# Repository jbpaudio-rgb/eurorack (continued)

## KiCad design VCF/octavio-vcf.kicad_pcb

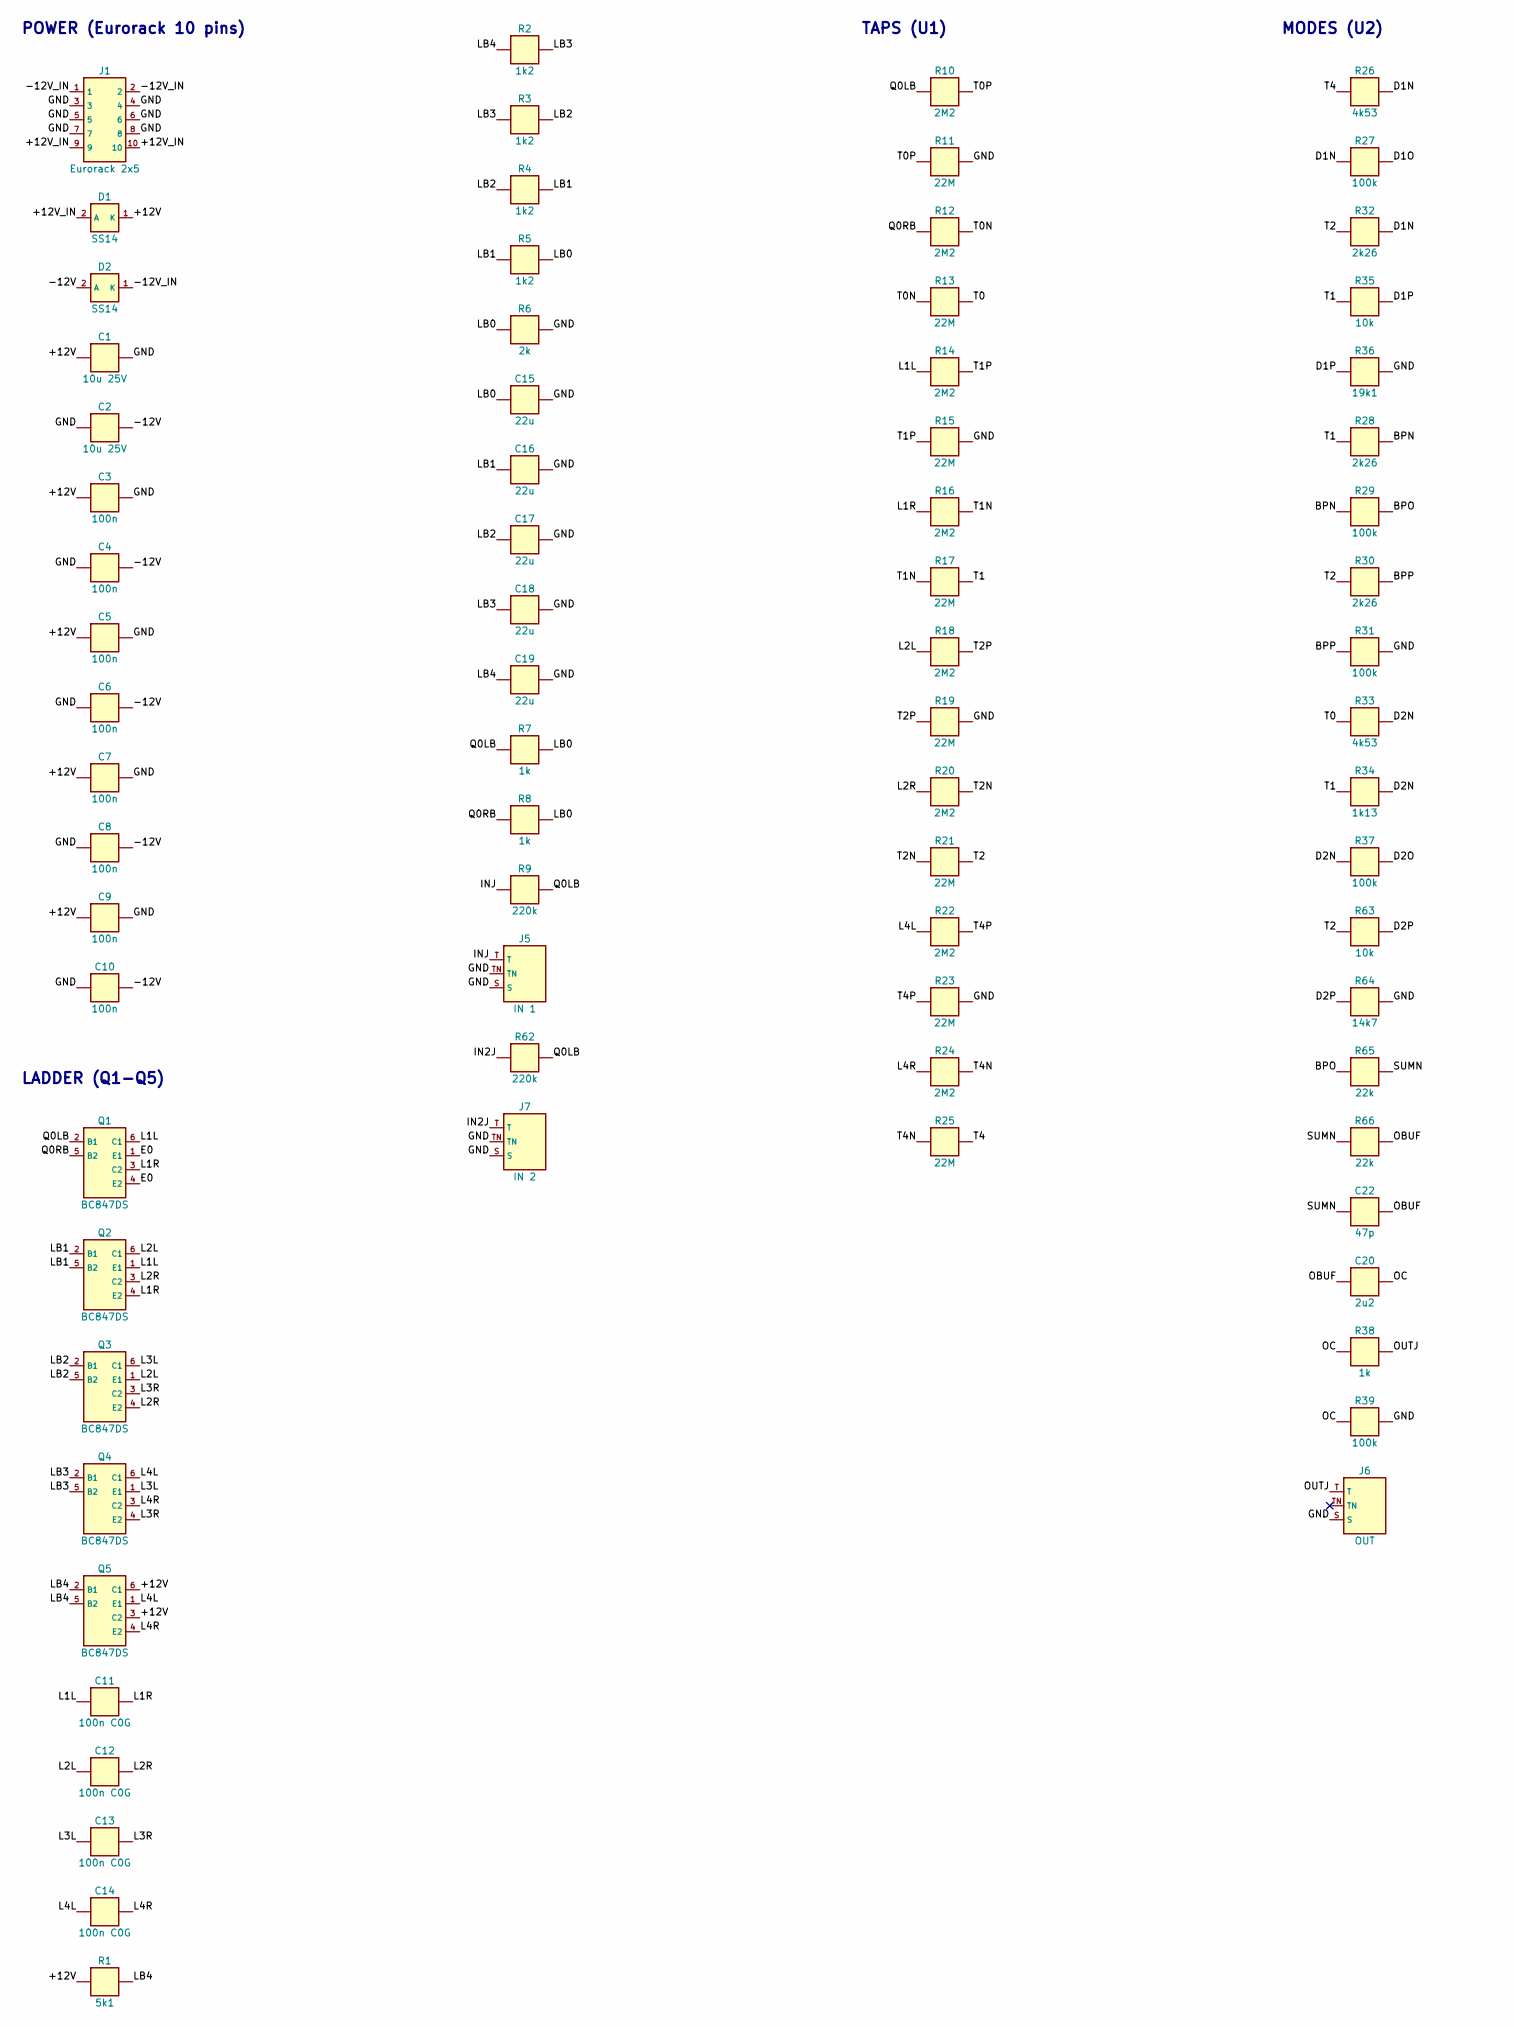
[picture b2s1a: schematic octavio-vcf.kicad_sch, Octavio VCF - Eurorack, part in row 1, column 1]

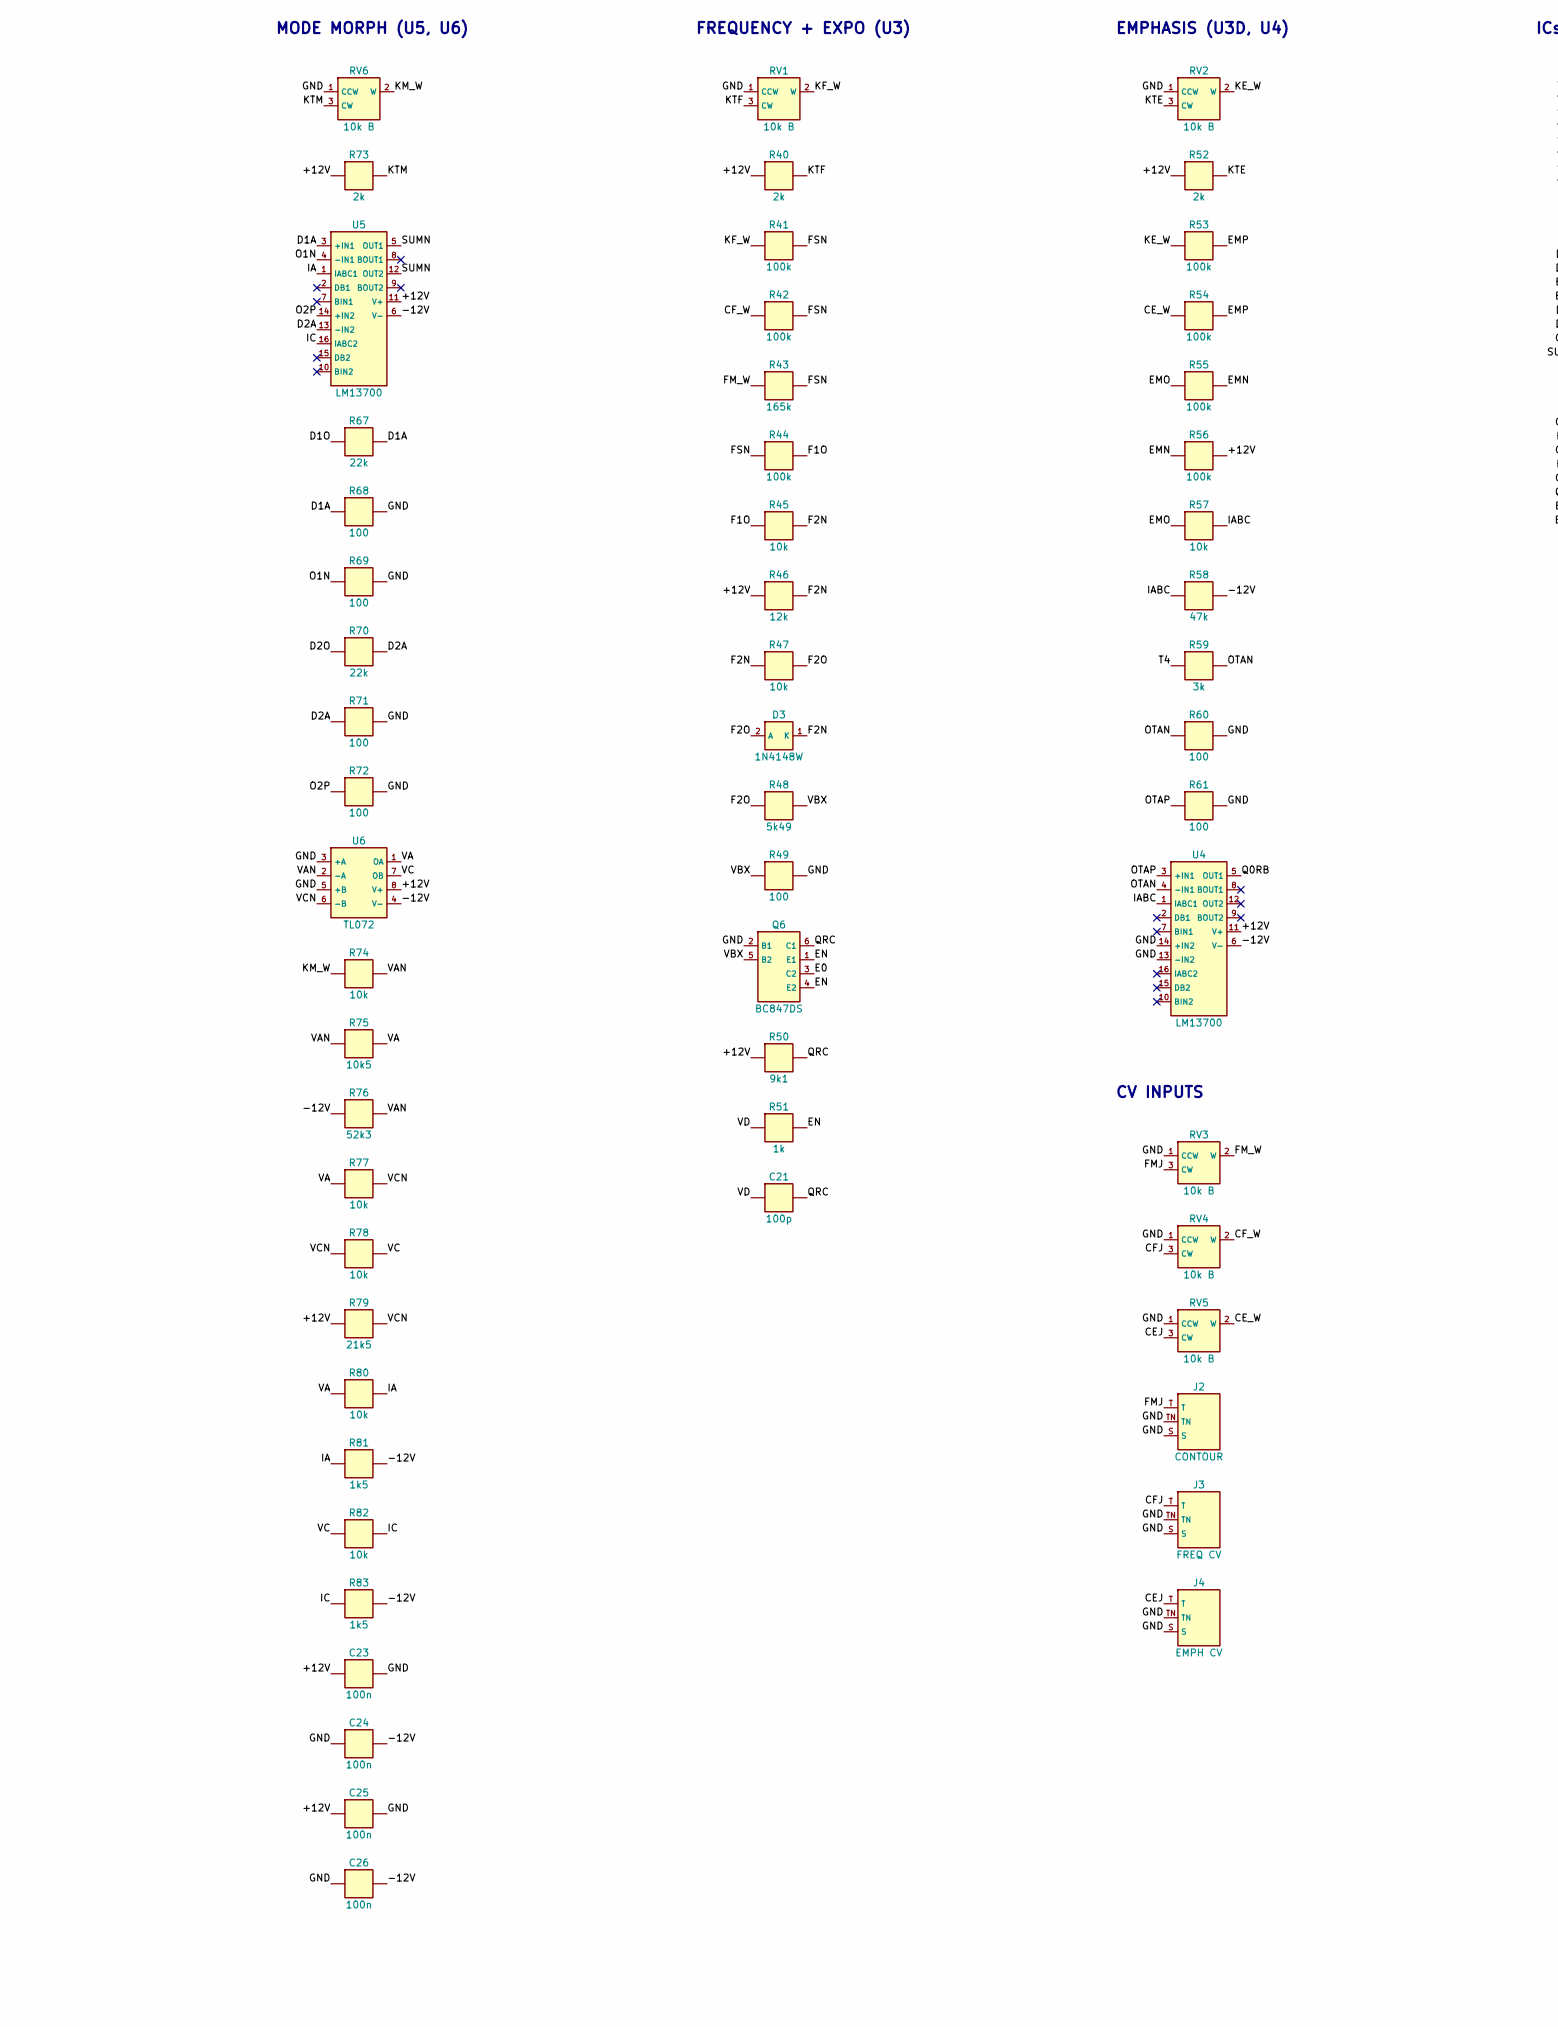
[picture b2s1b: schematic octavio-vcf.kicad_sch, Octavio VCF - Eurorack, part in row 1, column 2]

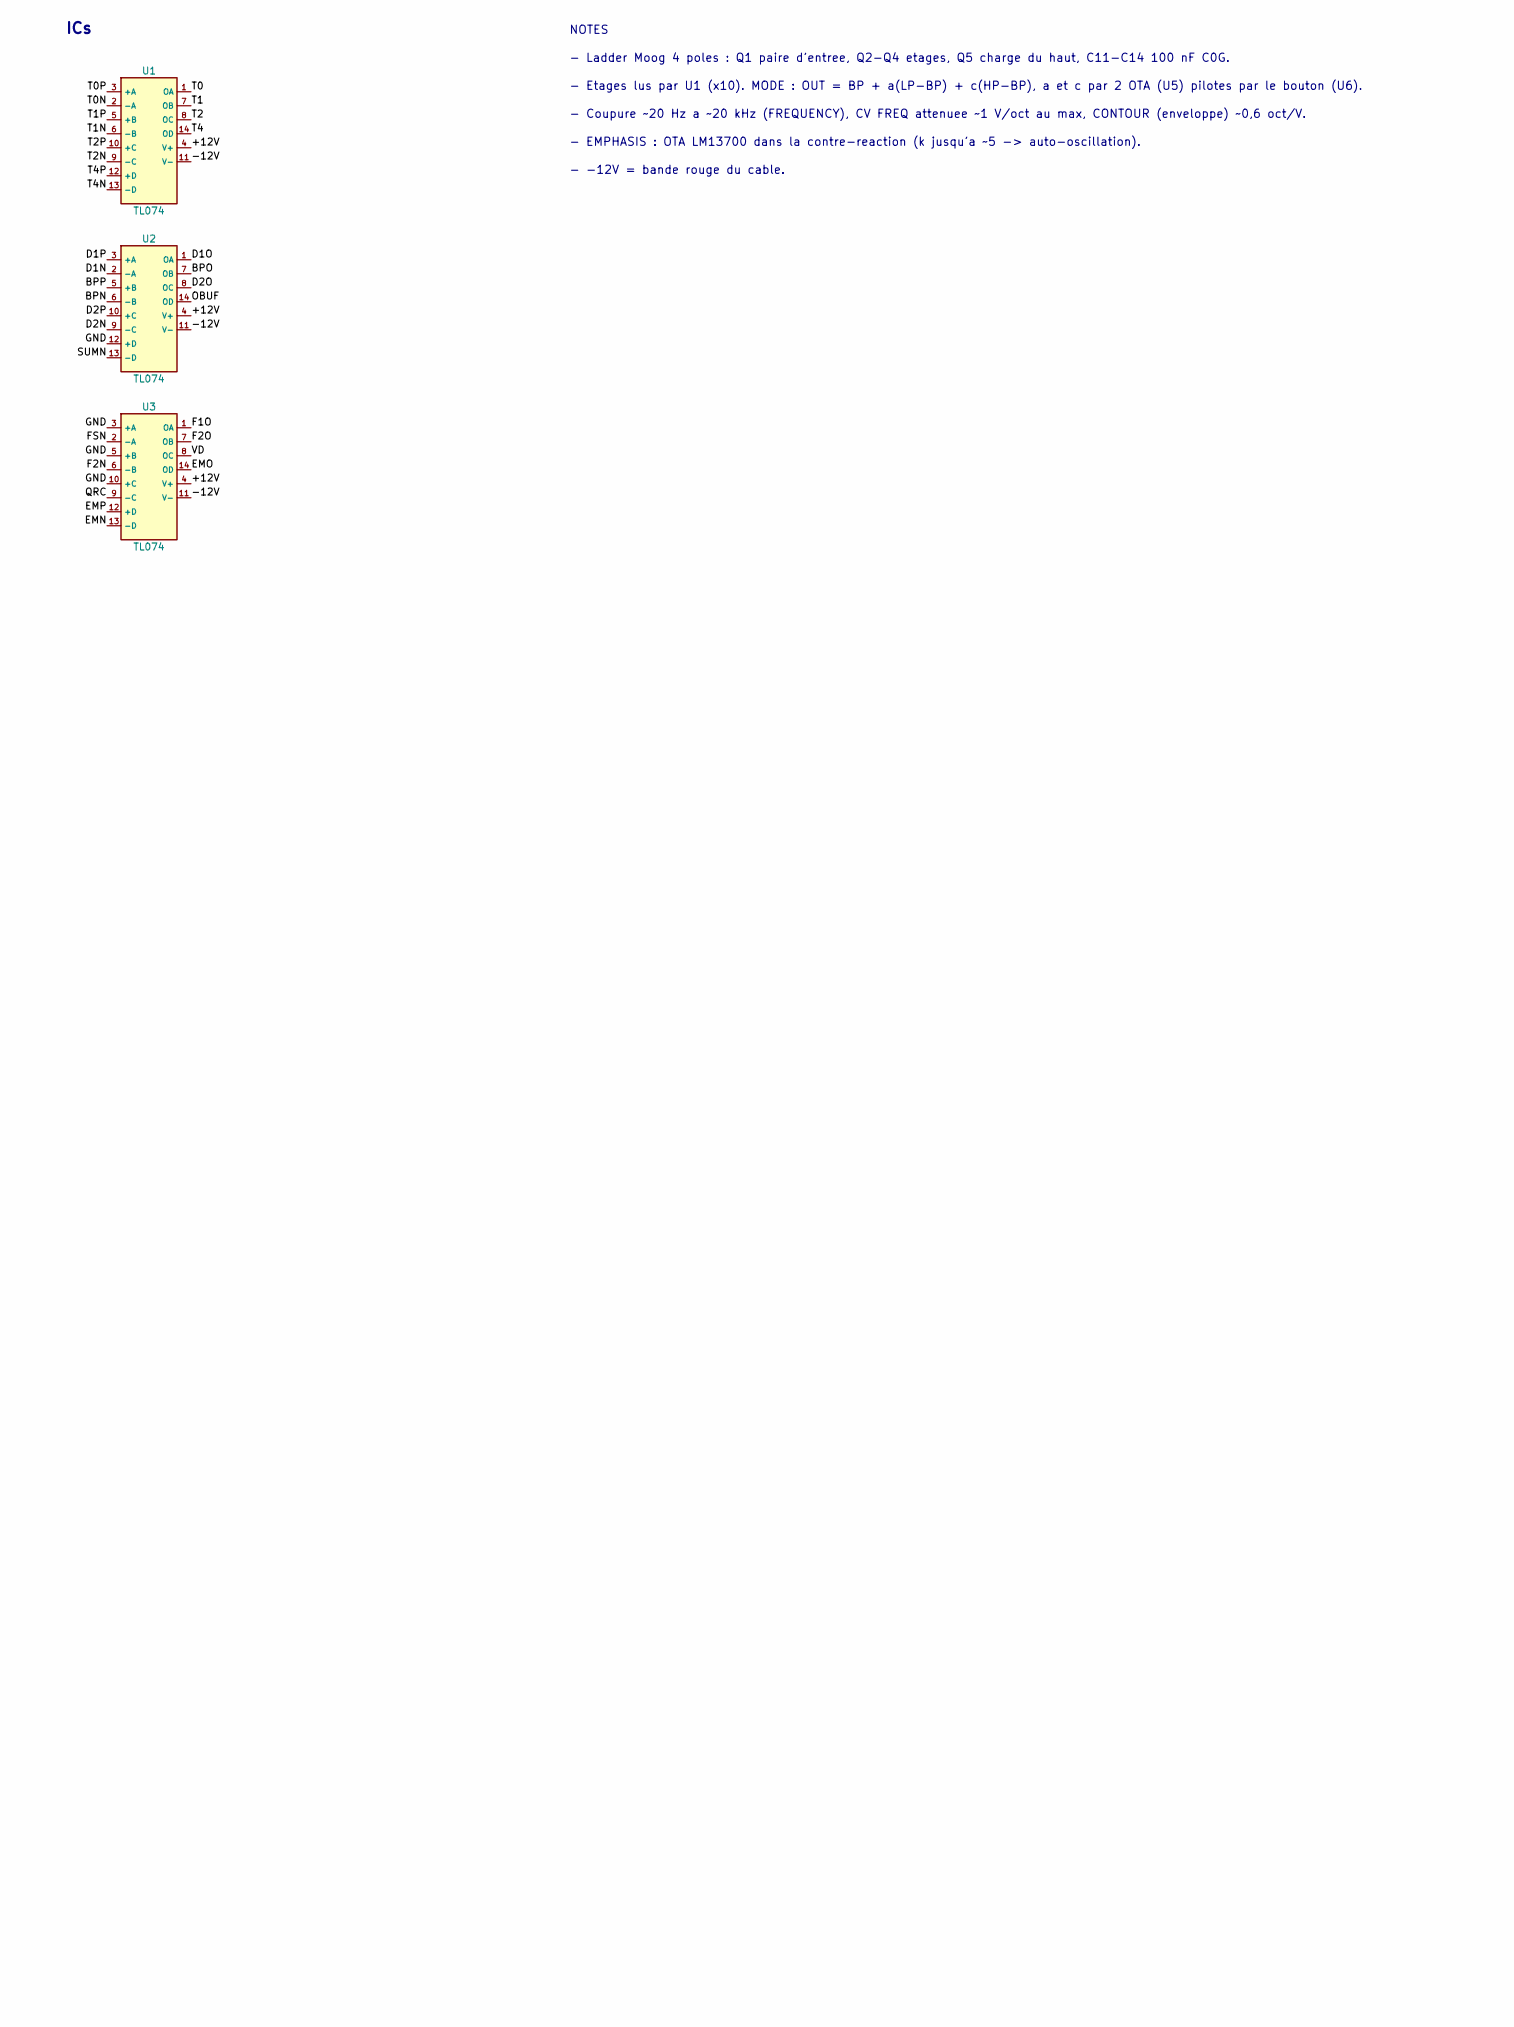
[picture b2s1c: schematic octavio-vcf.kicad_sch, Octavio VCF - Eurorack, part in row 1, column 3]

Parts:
C1, C2: 10u 25V; C_1206_3216Metric; MPN X5R/X7R 1206
C3, C4, C5, C6, C7, C8, C9, C10, C23, C24, C25, C26: 100n; C_0805_2012Metric
C11, C12, C13, C14: 100n C0G; C_1206_3216Metric; MPN 100 nF C0G/NP0 1206 2 % (condensateur d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
C15, C16, C17, C18, C19: 22u; C_1206_3216Metric; MPN X5R 1206 16 V
C20: 2u2; C_1206_3216Metric; MPN X7R 1206 25 V
C21: 100p; C_0805_2012Metric
C22: 47p; C_0805_2012Metric
D1, D2: SS14; D_SMA; MPN SS14 (40 V 1 A Schottky)
D3: 1N4148W; D_SOD-123; MPN 1N4148W
J1: Eurorack 2x5; IDC-Header_2x05_P2.54mm_Vertical; MPN Shrouded header 2x5 2.54 mm
J2: CONTOUR; Jack_3.5mm_Thonkiconn_PJ398SM; MPN QingPu WQP-PJ301M-12 (Thonkiconn)
J3: FREQ CV; Jack_3.5mm_Thonkiconn_PJ398SM; MPN QingPu WQP-PJ301M-12 (Thonkiconn)
J4: EMPH CV; Jack_3.5mm_Thonkiconn_PJ398SM; MPN QingPu WQP-PJ301M-12 (Thonkiconn)
J5: IN 1; Jack_3.5mm_Thonkiconn_PJ398SM; MPN QingPu WQP-PJ301M-12 (Thonkiconn)
J6: OUT; Jack_3.5mm_Thonkiconn_PJ398SM; MPN QingPu WQP-PJ301M-12 (Thonkiconn)
J7: IN 2; Jack_3.5mm_Thonkiconn_PJ398SM; MPN QingPu WQP-PJ301M-12 (Thonkiconn)
Q1, Q2, Q3, Q4, Q5, Q6: BC847DS; SOT-457; MPN BC847DS,115 (Nexperia, paire double)
R1: 5k1; R_0805_2012Metric
R2, R3, R4, R5: 1k2; R_0805_2012Metric
R6, R40, R52, R73: 2k; R_0805_2012Metric
R7, R8, R38, R51: 1k; R_0805_2012Metric
R9, R62: 220k; R_0805_2012Metric
R10, R12, R14, R16, R18, R20, R22, R24: 2M2; R_0805_2012Metric
R11, R13, R15, R17, R19, R21, R23, R25: 22M; R_0805_2012Metric
R26, R33: 4k53; R_0805_2012Metric
R27, R29, R31, R37, R39, R41, R42, R44, R53, R54, R55, R56: 100k; R_0805_2012Metric
R28, R30, R32: 2k26; R_0805_2012Metric
R34: 1k13; R_0805_2012Metric
R35, R45, R47, R57, R63, R74, R77, R78, R80, R82: 10k; R_0805_2012Metric
R36: 19k1; R_0805_2012Metric
R43: 165k; R_0805_2012Metric
R46: 12k; R_0805_2012Metric
R48: 5k49; R_0805_2012Metric
R49, R60, R61, R68, R69, R71, R72: 100; R_0805_2012Metric
R50: 9k1; R_0805_2012Metric
R58: 47k; R_0805_2012Metric
R59: 3k; R_0805_2012Metric
R64: 14k7; R_0805_2012Metric
R65, R66, R67, R70: 22k; R_0805_2012Metric
R75: 10k5; R_0805_2012Metric
R76: 52k3; R_0805_2012Metric
R79: 21k5; R_0805_2012Metric
R81, R83: 1k5; R_0805_2012Metric
RV1, RV2, RV3, RV4, RV5, RV6: 10k B; Pot_Alpha_9mm_Vertical; MPN POT-R09V-10K (9 mm vertical, B10k)
U1, U2, U3: TL074; SOIC-14_3.9x8.7mm_P1.27mm; MPN TL074CDR
U4, U5: LM13700; SOIC-16_3.9x9.9mm_P1.27mm; MPN LM13700MX/NOPB
U6: TL072; SOIC-8_3.9x4.9mm_P1.27mm; MPN TL072CDR

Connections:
+12V: C1.1, C3.1, C5.1, C7.1, C9.1, C23.1, C25.1, D1.1 (K), Q5.3 (C2), Q5.6 (C1), R1.1, R40.1, R46.1, R50.1, R52.1, R56.2, R73.1, R79.1, U1.4 (V+), U2.4 (V+), U3.4 (V+), U4.11 (V+), U5.11 (V+), U6.8 (V+)
+12V_IN: D1.2 (A), J1.9, J1.10
-12V: C2.2, C4.2, C6.2, C8.2, C10.2, C24.2, C26.2, D2.2 (A), R58.2, R76.1, R81.2, R83.2, U1.11 (V-), U2.11 (V-), U3.11 (V-), U4.6 (V-), U5.6 (V-), U6.4 (V-)
-12V_IN: D2.1 (K), J1.1, J1.2
BPN: R28.2, R29.1, U2.6 (-B)
BPO: R29.2, R65.1, U2.7 (OB)
BPP: R30.2, R31.1, U2.5 (+B)
CEJ: J4.T, RV5.3 (CW)
CE_W: R54.1, RV5.2 (W)
CFJ: J3.T, RV4.3 (CW)
CF_W: R42.1, RV4.2 (W)
D1A: R67.2, R68.1, U5.3 (+IN1)
D1N: R26.2, R27.1, R32.2, U2.2 (-A)
D1O: R27.2, R67.1, U2.1 (OA)
D1P: R35.2, R36.1, U2.3 (+A)
D2A: R70.2, R71.1, U5.13 (-IN2)
D2N: R33.2, R34.2, R37.1, U2.9 (-C)
D2O: R37.2, R70.1, U2.8 (OC)
D2P: R63.2, R64.1, U2.10 (+C)
E0: Q1.1 (E1), Q1.4 (E2), Q6.3 (C2)
EMN: R55.2, R56.1, U3.13 (-D)
EMO: R55.1, R57.1, U3.14 (OD)
EMP: R53.2, R54.2, U3.12 (+D)
EN: Q6.1 (E1), Q6.4 (E2), R51.2
F1O: R44.2, R45.1, U3.1 (OA)
F2N: D3.1 (K), R45.2, R46.2, R47.1, U3.6 (-B)
F2O: D3.2 (A), R47.2, R48.1, U3.7 (OB)
FMJ: J2.T, RV3.3 (CW)
FM_W: R43.1, RV3.2 (W)
FSN: R41.2, R42.2, R43.2, R44.1, U3.2 (-A)
GND: C1.2, C2.1, C3.2, C4.1, C5.2, C6.1, C7.2, C8.1, C9.2, C10.1, C15.2, C16.2, C17.2, C18.2, C19.2, C23.2, C24.1, C25.2, C26.1, J1.3, J1.4, J1.5, J1.6, J1.7, J1.8, J2.S, J2.TN, J3.S, J3.TN, J4.S, J4.TN, J5.S, J5.TN, J6.S, J7.S, J7.TN, Q6.2 (B1), R6.2, R11.2, R15.2, R19.2, R23.2, R31.2, R36.2, R39.2, R49.2, R60.2, R61.2, R64.2, R68.2, R69.2, R71.2, R72.2, RV1.1 (CCW), RV2.1 (CCW), RV3.1 (CCW), RV4.1 (CCW), RV5.1 (CCW), RV6.1 (CCW), U2.12 (+D), U3.3 (+A), U3.5 (+B), U3.10 (+C), U4.13 (-IN2), U4.14 (+IN2), U6.3 (+A), U6.5 (+B)
IABC: R57.2, R58.1, U4.1 (IABC1)
IN2J: J7.T, R62.1
INJ: J5.T, R9.1
KE_W: R53.1, RV2.2 (W)
KF_W: R41.1, RV1.2 (W)
KM_W: R74.1, RV6.2 (W)
KTE: R52.2, RV2.3 (CW)
KTF: R40.2, RV1.3 (CW)
KTM: R73.2, RV6.3 (CW)
L1L: C11.1, Q1.6 (C1), Q2.1 (E1), R14.1
L1R: C11.2, Q1.3 (C2), Q2.4 (E2), R16.1
L2L: C12.1, Q2.6 (C1), Q3.1 (E1), R18.1
L2R: C12.2, Q2.3 (C2), Q3.4 (E2), R20.1
L3L: C13.1, Q3.6 (C1), Q4.1 (E1)
L3R: C13.2, Q3.3 (C2), Q4.4 (E2)
L4L: C14.1, Q4.6 (C1), Q5.1 (E1), R22.1
L4R: C14.2, Q4.3 (C2), Q5.4 (E2), R24.1
LB0: C15.1, R5.2, R6.1, R7.2, R8.2
LB1: C16.1, Q2.2 (B1), Q2.5 (B2), R4.2, R5.1
LB2: C17.1, Q3.2 (B1), Q3.5 (B2), R3.2, R4.1
LB3: C18.1, Q4.2 (B1), Q4.5 (B2), R2.2, R3.1
LB4: C19.1, Q5.2 (B1), Q5.5 (B2), R1.2, R2.1
O1N: R69.1, U5.4 (-IN1)
O2P: R72.1, U5.14 (+IN2)
OBUF: C20.1, C22.2, R66.2, U2.14 (OD)
OC: C20.2, R38.1, R39.1
OTAN: R59.2, R60.1, U4.4 (-IN1)
OTAP: R61.1, U4.3 (+IN1)
OUTJ: J6.T, R38.2
Q0LB: Q1.2 (B1), R7.1, R9.2, R10.1, R62.2
Q0RB: Q1.5 (B2), R8.1, R12.1, U4.5 (OUT1)
QRC: C21.2, Q6.6 (C1), R50.2, U3.9 (-C)
SUMN: C22.1, R65.2, R66.1, U2.13 (-D), U5.5 (OUT1), U5.12 (OUT2)
T0: R13.2, R33.1, U1.1 (OA)
T0N: R12.2, R13.1, U1.2 (-A)
T0P: R10.2, R11.1, U1.3 (+A)
T1: R17.2, R28.1, R34.1, R35.1, U1.7 (OB)
T1N: R16.2, R17.1, U1.6 (-B)
T1P: R14.2, R15.1, U1.5 (+B)
T2: R21.2, R30.1, R32.1, R63.1, U1.8 (OC)
T2N: R20.2, R21.1, U1.9 (-C)
T2P: R18.2, R19.1, U1.10 (+C)
T4: R25.2, R26.1, R59.1, U1.14 (OD)
T4N: R24.2, R25.1, U1.13 (-D)
T4P: R22.2, R23.1, U1.12 (+D)
VA: R75.2, R77.1, R80.1, U6.1 (OA)
VAN: R74.2, R75.1, R76.2, U6.2 (-A)
VBX: Q6.5 (B2), R48.2, R49.1
VC: R78.2, R82.1, U6.7 (OB)
VCN: R77.2, R78.1, R79.2, U6.6 (-B)
VD: C21.1, R51.1, U3.8 (OC)

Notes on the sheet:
POWER (Eurorack 10 pins)
LADDER (Q1-Q5)
TAPS (U1)
MODES (U2)
MODE MORPH (U5, U6)
FREQUENCY + EXPO (U3)
EMPHASIS (U3D, U4)
CV INPUTS
ICs
NOTES
- Ladder Moog 4 poles : Q1 paire d'entree, Q2-Q4 etages, Q5 charge du haut, C11-C14 100 nF C0G.
- Etages lus par U1 (x10). MODE : OUT = BP + a(LP-BP) + c(HP-BP), a et c par 2 OTA (U5) pilotes par le bouton (U6).
- Coupure ~20 Hz a ~20 kHz (FREQUENCY), CV FREQ attenuee ~1 V/oct au max, CONTOUR (enveloppe) ~0,6 oct/V.
- EMPHASIS : OTA LM13700 dans la contre-reaction (k jusqu'a ~5 -> auto-oscillation).
- -12V = bande rouge du cable.

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
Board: 2 copper layers, 139 parts (127 on the bottom side), 86 nets, no tracks yet.

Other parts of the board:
RV7, RV8: 2k; Trim_SMD_Bourns_3314J

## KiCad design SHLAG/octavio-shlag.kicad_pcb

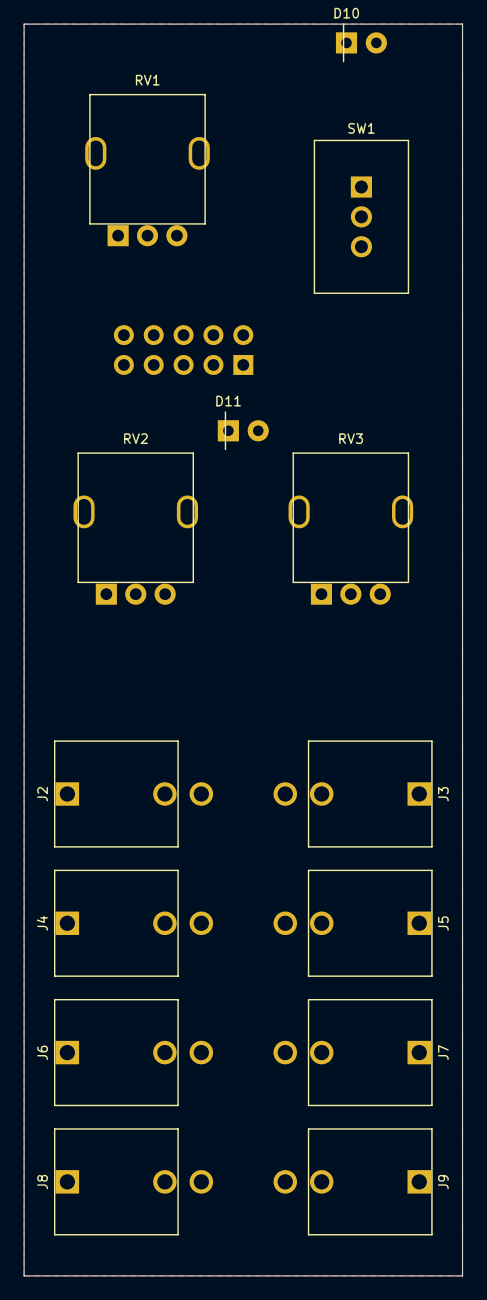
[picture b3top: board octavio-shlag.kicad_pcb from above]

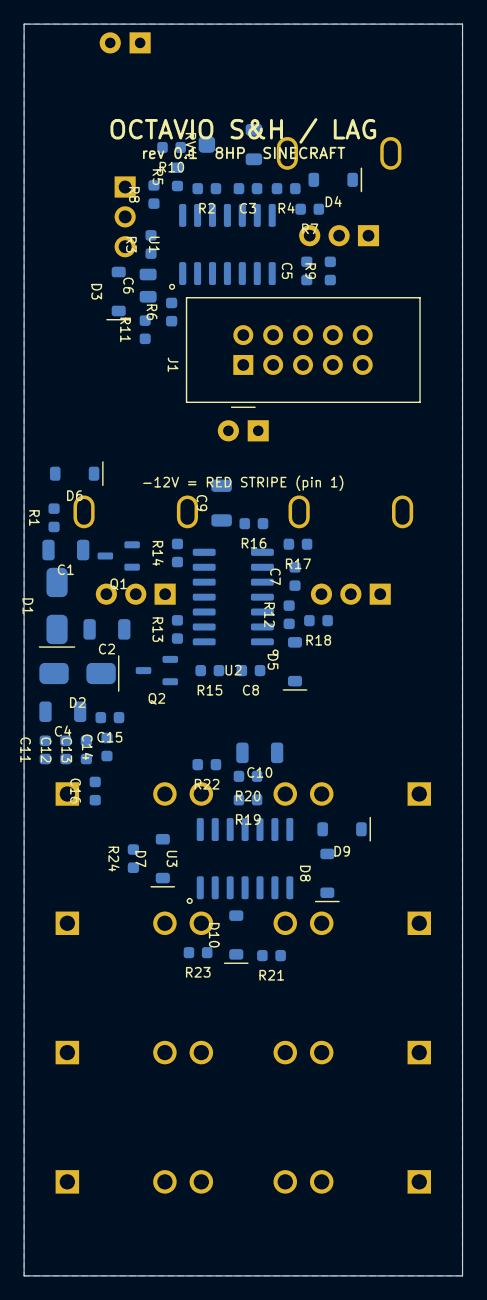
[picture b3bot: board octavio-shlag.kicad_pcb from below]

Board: 2 copper layers, 37.3 x 106.5 mm, 71 parts (57 on the bottom side), 47 nets, no tracks yet.

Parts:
C1, C2, C4: 10u 25V; C_1206_3216Metric
C3: 1u; C_0603_1608Metric
C5: 22p; C_0603_1608Metric
C6: 47n C0G; C_0805_2012Metric
C7, C11, C12, C13, C14, C15, C16: 100n; C_0603_1608Metric
C8: 1n C0G; C_0603_1608Metric
C9: 100n C0G; C_1206_3216Metric
C10: 2u2; C_1206_3216Metric
D1, D2: SS14; D_SMA
D3, D4, D5, D6, D7, D8, D9, D10#2: 1N4148W; D_SOD-123
D10, D11: LED; LED_D3.0mm
J1: Eurorack 2x5; IDC-Header_2x05_P2.54mm_Vertical
J2: S&H IN; Jack_3.5mm_Thonkiconn_PJ398SM
J3: TRIG; Jack_3.5mm_Thonkiconn_PJ398SM
J4: NOISE; Jack_3.5mm_Thonkiconn_PJ398SM
J5: CLOCK; Jack_3.5mm_Thonkiconn_PJ398SM
J6: S&H OUT; Jack_3.5mm_Thonkiconn_PJ398SM
J7: GATE; Jack_3.5mm_Thonkiconn_PJ398SM
J8: LAG IN; Jack_3.5mm_Thonkiconn_PJ398SM
J9: LAG OUT; Jack_3.5mm_Thonkiconn_PJ398SM
Q1: BC847; SOT-23
Q2: MMBFJ112; SOT-23
R1, R2, R5, R7, R12, R15, R16, R17: 100k; R_0603_1608Metric
R3, R4, R10, R18, R20, R21, R22, R23: 1k; R_0603_1608Metric
R6: 22M; R_0603_1608Metric
R8: 200k; R_0603_1608Metric
R9, R14, R19: 10k; R_0603_1608Metric
R11, R24: 2k2; R_0603_1608Metric
R13: 15k; R_0603_1608Metric
RV1: 10k A; Pot_Alpha_9mm_Vertical
RV2, RV3: 1M A; Pot_Alpha_9mm_Vertical
RV4: 200k; Trim_SMD_Bourns_3314J
SW1: S&H / T&H; Toggle_SPDT_Dailywell_2MS1
U1, U2, U3: TL074; SOIC-14_3.9x8.7mm_P1.27mm

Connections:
+12V: C1.1, C11.1, C13.1, C15.1, D1.1, D3.1, D7.1, R1.1, R12.1, U1.4, U2.4, U3.4
+12V_IN: D1.2, J1.9, J1.10
-12V: C2.2, C12.2, C14.2, C16.2, D2.2, D5.2, R16.2, U1.11, U2.11, U3.11
-12V_IN: D2.1, J1.1, J1.2
CB: J3.TN, R10.1, R11.1, U1.13, U1.14
CB_A: D10.2, R11.2
CLKL: D3.2, D4.1, R9.2, U1.12
CLOCKJ: J5.T, R10.2
GATEJ: J7.T, R20.2
GB: R20.1, U3.6, U3.7
GND: C1.2, C2.1, C4.2, C7.2, C9.2, C10.2, C11.2, C12.1, C13.2, C14.1, C15.2, C16.1, D4.2, D8.2, D10.1, D11.1, J1.3, J1.4, J1.5, J1.6, J1.7, J1.8, J2.S, J3.S, J4.S, J5.S, J6.S, J7.S, J8.S, J9.S, Q1.1, R2.2, R13.2, R15.2, RV1.1, U1.5, U1.9, U2.6, U3.2
GTC: R19.1, U3.1
GTL: D7.2, D8.1, R19.2, U3.5
HOLD: C9.1, Q2.2, U2.12
INTN: C6.1, R5.2, R6.2, U1.6
JG: D6.2, Q2.3, R17.1
LAGC: C10.1, R21.2, R22.2, U3.12
LAGINJ: J8.T, U3.10
LAGOUTJ: J9.T, R23.2
LCMP: D9.2, D10#2.1, U3.8
LF1: D10#2.2, RV3.1
LF2: R22.1, RV3.2, RV3.3
LO: R23.1, R24.1, U3.9, U3.13, U3.14
LO_A: D11.2, R24.2
LR1: D9.1, RV2.1
LR2: R21.1, RV2.2, RV2.3
NA: C3.2, R2.1, U1.3
NG: C5.2, R3.1, RV4.2, RV4.3, U1.2
NGC: C4.1, R3.2
NOISEJ: J4.T, R4.2
NZ: C3.1, Q1.2, R1.2
RATEW: R5.1, RV1.2
REF: C7.1, R12.2, R13.1, U2.2
SCH: R7.2, R8.2, U1.10
SHC: SW1.1, U2.7
SHCTL: D6.1, SW1.2
SHINJ: J2.T, U2.10
SHIN_B: Q2.1, R17.2, U2.8, U2.9
SHOUTJ: J6.T, R18.2
SHP: C8.2, D5.1, R16.1, U2.5
SH_O: J8.TN, R18.1, U2.13, U2.14, U3.3
SQ: R6.1, R8.1, R9.1, RV1.3, U1.8
TRC: C8.1, SW1.3, U2.1
TRGR: R14.2, R15.1, U2.3
TRI: C6.2, R7.1, U1.7
TRIGJ: J3.T, R14.1
WN_O: C5.1, J2.TN, R4.1, RV4.1, U1.1

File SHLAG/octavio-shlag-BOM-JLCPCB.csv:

Comment,Designator,Footprint,LCSC Part #,Notes
10u 25V X5R/X7R 1206,"C1,C2,C4",C_1206_3216Metric,,X5R/X7R 1206 - SMT bottom - laisser JLC choisir (Basic de preference)
2u2 X7R 1206 25 V,C10,C_1206_3216Metric,,X7R 1206 25 V - SMT bottom - laisser JLC choisir (Basic de preference)
1u X7R 0603 25 V,C3,C_0603_1608Metric,,X7R 0603 25 V - SMT bottom - laisser JLC choisir (Basic de preference)
22p,C5,C_0603_1608Metric,,SMT bottom - laisser JLC choisir (Basic de preference)
47n C0G C0G/NP0 0805,C6,C_0805_2012Metric,,C0G/NP0 0805 - SMT bottom - laisser JLC choisir (Basic de preference)
100n,"C7,C11,C12,C13,C14,C15,C16",C_0603_1608Metric,,SMT bottom - laisser JLC choisir (Basic de preference)
1n C0G C0G/NP0 0603,C8,C_0603_1608Metric,,C0G/NP0 0603 - SMT bottom - laisser JLC choisir (Basic de preference)
100n C0G C0G/NP0 1206,C9,C_1206_3216Metric,,"C0G/NP0 1206 (condensateur de maintien, très faible fuite) - SMT bottom - laisser JLC choisir (Basic de preference)"
SS14,"D1,D2",D_SMA,,SS14 (40 V 1 A Schottky) - SMT bottom - laisser JLC choisir (Basic de preference)
LED,D10,LED_D3.0mm,,LED 3 mm ambre (CLOCK) - THT (wave soldering) - laisser JLC choisir (Basic de preference)
LED,D11,LED_D3.0mm,,"LED 3 mm rouge (LAG, positif) - THT (wave soldering) - laisser JLC choisir (Basic de preference)"
1N4148W,"D3,D4,D5,D6,D7,D8,D9,D10",D_SOD-123,,1N4148W - SMT bottom - laisser JLC choisir (Basic de preference)
Eurorack 2x5,J1,IDC-Header_2x05_P2.54mm_Vertical,,Shrouded header 2x5 2.54 mm - THT (wave soldering) - laisser JLC choisir (Basic de preference)
S&H IN,J2,Jack_3.5mm_Thonkiconn_PJ398SM,C9900080080,QingPu WQP-PJ301M-12 (Thonkiconn) - THT (wave soldering)
TRIG,J3,Jack_3.5mm_Thonkiconn_PJ398SM,C9900080080,QingPu WQP-PJ301M-12 (Thonkiconn) - THT (wave soldering)
NOISE,J4,Jack_3.5mm_Thonkiconn_PJ398SM,C9900080080,QingPu WQP-PJ301M-12 (Thonkiconn) - THT (wave soldering)
CLOCK,J5,Jack_3.5mm_Thonkiconn_PJ398SM,C9900080080,QingPu WQP-PJ301M-12 (Thonkiconn) - THT (wave soldering)
S&H OUT,J6,Jack_3.5mm_Thonkiconn_PJ398SM,C9900080080,QingPu WQP-PJ301M-12 (Thonkiconn) - THT (wave soldering)
GATE,J7,Jack_3.5mm_Thonkiconn_PJ398SM,C9900080080,QingPu WQP-PJ301M-12 (Thonkiconn) - THT (wave soldering)
LAG IN,J8,Jack_3.5mm_Thonkiconn_PJ398SM,C9900080080,QingPu WQP-PJ301M-12 (Thonkiconn) - THT (wave soldering)
LAG OUT,J9,Jack_3.5mm_Thonkiconn_PJ398SM,C9900080080,QingPu WQP-PJ301M-12 (Thonkiconn) - THT (wave soldering)
BC847C,Q1,SOT-23,,BC847C (jonction base-émetteur en avalanche = source de bruit) - SMT bottom - laisser JLC choisir (Basic de preference)
MMBFJ112,Q2,SOT-23,,"MMBFJ112 (JFET N, D-S-G) - SMT bottom - laisser JLC choisir (Basic de preference)"
100k 1% 0805,"R1,R2,R5,R7,R12,R15,R16",R_0603_1608Metric,,SMT bottom - laisser JLC choisir (Basic de preference)
2k2 1% 0805,"R11,R24",R_0603_1608Metric,,SMT bottom - laisser JLC choisir (Basic de preference)
15k 1% 0805,R13,R_0603_1608Metric,,SMT bottom - laisser JLC choisir (Basic de preference)
1M 1% 0805,R17,R_0603_1608Metric,,SMT bottom - laisser JLC choisir (Basic de preference)
1k 1% 0805,"R3,R4,R10,R18,R20,R21,R22,R23",R_0603_1608Metric,,SMT bottom - laisser JLC choisir (Basic de preference)
22M 1% 0805,R6,R_0603_1608Metric,,SMT bottom - laisser JLC choisir (Basic de preference)
200k 1% 0805,R8,R_0603_1608Metric,,SMT bottom - laisser JLC choisir (Basic de preference)
10k 1% 0805,"R9,R14,R19",R_0603_1608Metric,,SMT bottom - laisser JLC choisir (Basic de preference)
10k A,RV1,Pot_Alpha_9mm_Vertical,,"POT-R09V-10K A (9 mm vertical, log) - THT (wave soldering) - laisser JLC choisir (Basic de preference)"
1M A,"RV2,RV3",Pot_Alpha_9mm_Vertical,,"POT-R09V-1M A (9 mm vertical, log) - THT (wave soldering) - laisser JLC choisir (Basic de preference)"
200k Bourns 3314J-1-204E,RV4,Trim_SMD_Bourns_3314J,,Bourns 3314J-1-204E (niveau du bruit : 10 V crête à crête) - SMT bottom - laisser JLC choisir (Basic de preference)
S&H / T&H,SW1,Toggle_SPDT_Dailywell_2MS1,,"Dailywell 2MS1T1B1M2QES (SPDT ON-ON) : haut = S&H, bas = T&H - THT (wave soldering) - laisser JLC choisir (Basic de preference)"
TL074CDR,"U1,U2,U3",SOIC-14_3.9x8.7mm_P1.27mm,C12594,TL074CDR - SMT bottom

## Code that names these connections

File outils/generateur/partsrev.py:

# Octavio SPRING REVERB - driver + recovery for an Accutronics / Belton 3-spring tank, Eurorack 10 HP.
# DRIVE sets how hard the springs are hit (PEAK LED), TONE darkens the return, MIX crossfades dry / wet and is
# voltage controlled (MIX CV with attenuator) through a PNP pair splitting one current between two OTAs (LM13700).
# SEND / RETURN : effects loop on the wet path (RETURN is normalled to the tank).
import sys; sys.path.insert(0, "/home/claude/work")
from modbase import *

HP = 10
PANEL_W = 50.5
PANEL_H = 128.5
NAME = "SPRING REVERB"; TITLE = "REVERB"; REV = "0.1"; FOLDER = "SPRINGREVERB"; PROJ = "octavio-springreverb"; SHORT = "springreverb"
DESC = "Spring reverb (tank 4FB3C1B), DRIVE, TONE, voltage-controlled MIX, send / return"
GRID = [(x, y) for y in (32, 58) for x in (14, 37)]
J1A = (25.25, 70.0)

cx = PANEL_W / 2
DRK, TNK = (12.6, 22.0), (37.9, 22.0)
MXK, CVK = (12.6, 53.0), (37.9, 53.0)
PEAK = (cx, 21.0)
JX = (9.0, cx, 41.5)
JY = (95.5, 109.5)
POT100B = "POT-R09V-100K (9 mm vertical, B100k)"

power()

SEC[0] = "INPUT + DRIVE"
opamp("GND", "INN", "DRY")                              # DRY = -IN, 100k input
R("100k", "INJ", "INN"); R("100k", "DRY", "INN")
C("1u", "DRY", "DA", "X7R 0603 25 V"); R("22k", "DA", "DN")
opamp("GND", "DN", "DRV")                               # gain 0.2 .. 4.8
R("4k7", "DN", "DF")
pot("RV1", "100k A", DRK, "DF", "DRV", "DRV", "POT-R09V-100K A (9 mm vertical, log)")
C("22p C0G", "DRV", "DN", "C0G/NP0 0603")
R("1k", "DRV", "SENDJ")
led("D10", PEAK, "DRV", "LED 3 mm rouge (PEAK : s'allume quand les ressorts sont bien attaqués)")

SEC[0] = "TANK DRIVER + RECOVERY (NE5532)"
add("U3", "NE5532", "TL072", SOIC8, "B", None, 0,
    {"3": "DRV", "2": "TKD", "1": "TKD", "5": "TANKOUT", "6": "RN", "7": "REC", "8": "+12V", "4": "-12V"}, "NE5532DR (double ampli bas bruit, sortie 30 mA)")
C("100n", "+12V", "GND"); C("100n", "GND", "-12V")
R("47R", "TKD", "TANKIN")
add("J10", "TANK IN", "CONN2", JST2, "B", None, 0, {"1": "TANKIN", "2": "GND"}, "JST PH 2 broches (câble blindé vers la fiche RCA IN de la cuve)")
add("J11", "TANK OUT", "CONN2", JST2, "B", None, 0, {"1": "TANKOUT", "2": "GND"}, "JST PH 2 broches (câble blindé vers la fiche RCA OUT de la cuve)")
R("47k", "TANKOUT", "GND")
R("100k", "REC", "RN"); C("100p C0G", "REC", "RN", "C0G/NP0 0603")
R("1k", "RN", "RNC"); C("10u 25V", "RNC", "GND", "X5R/X7R 1206", C1206)

SEC[0] = "TONE + RETURN"
C("1u", "REC", "RA", "X7R 0603 25 V"); R("10k", "RA", "TN")
opamp("GND", "TN", "WETA")
R("22k", "WETA", "TN"); C("4n7 C0G", "TN", "TC", "C0G/NP0 0603")
pot("RV2", "100k B", TNK, "TC", "WETA", "WETA", POT100B)
R("1M", "RETJ", "GND")
opamp("RETJ", "WB", "WB")
R("1k", "WB", "WETJ")

SEC[0] = "MIX CONTROL (PNP PAIR)"
pot("RV3", "10k B", MXK, "-12V", "MXW", "+12V", "POT-R09V-10K B (9 mm vertical)")
pot("RV4", "100k B", CVK, "GND", "CVW", "MIXCVJ", POT100B)
opamp("GND", "MSN", "MCTL")
R("100k", "MXW", "MSN"); R("100k", "CVW", "MSN"); R("47k", "MCTL", "MSN")
R("100k", "MCTL", "PB1"); R("2k2", "PB1", "GND"); R("2k2", "PB2", "GND")
add("Q1", "BCM857DS", "DUALPNP", SOT457, "B", None, 0,
    {"1": "TAIL", "2": "PB1", "3": "IAD", "4": "TAIL", "5": "PB2", "6": "IAW"}, "BCM857DS,115 (Nexperia, paire PNP appairée)")
R("56k", "+12V", "TAIL")

SEC[0] = "VCA CROSSFADE (LM13700)"
add("U4", "LM13700", "LM13700", SOIC16, "B", None, 0,
    {"1": "IAW", "2": None, "3": "OWP", "4": "OWM", "5": "OTAS", "6": "-12V", "7": "-12V", "8": None,
     "9": None, "10": "-12V", "11": "+12V", "12": "OTAS", "13": "ODM", "14": "ODP", "15": None, "16": "IAD"}, "LM13700MX/NOPB")
C("100n", "+12V", "GND"); C("100n", "GND", "-12V")
R("220k", "WB", "OWP"); R("470R", "OWP", "GND"); R("470R", "OWM", "GND")
R("220k", "DRY", "ODP"); R("470R", "ODP", "GND"); R("470R", "ODM", "GND")
opamp("GND", "OTAS", "MIXO")
R("120k", "MIXO", "OTAS"); C("22p C0G", "MIXO", "OTAS", "C0G/NP0 0603")
R("1k", "MIXO", "OUTJ")

SEC[0] = "JACKS"
jack("J2", "IN", (JX[0], JY[0]), "INJ"); jack("J3", "SEND", (JX[1], JY[0]), "SENDJ"); jack("J4", "RETURN", (JX[2], JY[0]), "RETJ", "WETA")
jack("J5", "MIX CV", (JX[0], JY[1]), "MIXCVJ"); jack("J6", "WET", (JX[1], JY[1]), "WETJ"); jack("J7", "OUT", (JX[2], JY[1]), "OUTJ")

BLOCKS = finish()

NOTES = ["- Cuve conseillee : Accutronics 4FB3C1B (longue, 3 ressorts, entree 1475 ohms, sortie 2250 ohms, entree isolee / sortie a la masse).",
         "- Driver : NE5532 en suiveur, 47 ohms -> bobine d'entree (jusqu'a ~7 mA). Recuperation : NE5532 gain x101.",
         "- TONE : passe-bas variable (22k // 4n7 + pot 100k) ; a fond = brillant, au minimum = sombre (~1,5 kHz).",
         "- MIX : la paire PNP BCM857DS partage ~200 uA entre les deux OTA du LM13700 (sec / humide) ; MIX + MIX CV (attenuateur) pilotent les bases.",
         "- SEND = signal qui attaque la cuve ; RETURN remplace le retour de la cuve (normalise dessus) -> boucle d'effet.",
         "- La cuve se fixe dans le boitier (pas sur le module) ; deux cables blindes RCA -> JST PH.",
         "- -12V = bande rouge du cable."]

def panel_art(T, knob_scale, TICKS):
    T("SPRING TANK", cx, 8.4, 0.85, 0.15)
    T("DRIVE", DRK[0], DRK[1] - 9.4, 0.75, 0.13); T("TONE", TNK[0], TNK[1] - 9.4, 0.75, 0.13)
    scale(T, TICKS, DRK[0], DRK[1], ["0", "", "4", "6", "", "10"])
    scale(T, TICKS, TNK[0], TNK[1], [""] * 6)
    T("DARK", TNK[0] - 7.4, TNK[1] + 8.6, 0.6, 0.12); T("BRIGHT", TNK[0] + 7.0, TNK[1] + 8.6, 0.6, 0.12)
    T("PEAK", PEAK[0], PEAK[1] + 3.6, 0.6, 0.12)
    T("MIX", MXK[0], MXK[1] - 9.4, 0.75, 0.13); T("MIX CV", CVK[0], CVK[1] - 9.4, 0.75, 0.13)
    scale(T, TICKS, MXK[0], MXK[1], [""] * 11, r1=6.0, r2=6.8)
    T("DRY", MXK[0] - 7.2, MXK[1] + 8.6, 0.6, 0.12); T("WET", MXK[0] + 7.2, MXK[1] + 8.6, 0.6, 0.12)
    scale(T, TICKS, CVK[0], CVK[1], ["0", "", "4", "6", "", "10"])
    for (lab, x, y) in (("IN", JX[0], JY[0]), ("SEND", JX[1], JY[0]), ("RETURN", JX[2], JY[0]),
                        ("MIX CV", JX[0], JY[1]), ("WET", JX[1], JY[1]), ("OUT", JX[2], JY[1])):
        T(lab, x, y - 6.0, 0.75, 0.13)

DIV = [(1.2, 36.0, PANEL_W - 1.2, 36.0), (1.2, 82.5, PANEL_W - 1.2, 82.5)]

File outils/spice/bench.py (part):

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        say(f'  IN 1 = ±5 V, MASTER à fond : OUT de {a[2]:.2f} à {a[3]:.2f} V, 3e harmonique {20 * np.log10(at(f, S, 3000) / at(f, S, 1000)):.0f} dB (saturation douce)')

def NOISETOOLS():
    d = sim('NOISETOOLS', 'clk', T('NOISETOOLS', 0.4, step=20e-6, osc=True, drive={'J5': 'SIN(0 5 3)'}, pots={'RV1': 0.6, 'RV2': 0.3}), ['PULSEJ', 'SHOUTJ', 'SLOUTJ', 'WHITEJ', 'PINKJ'])
    if d:
        say(f'  PULSE : {freq(d, "PULSEJ", 0.05):.1f} Hz, de {d["PULSEJ"].min():.2f} à {d["PULSEJ"].max():.2f} V')
        t, v = win(d, 'SHOUTJ', 0.05); steps = np.sum(np.abs(np.diff(v)) > 0.05)
        say(f'  S&H (entrée = sinus 3 Hz, TRIG = PULSE) : {steps} paliers, de {v.min():.2f} à {v.max():.2f} V ; SLEW de {d["SLOUTJ"].min():.2f} à {d["SLOUTJ"].max():.2f} V')
        say(f'  bruit (SPICE ne fait pas de bruit d avalanche : on vérifie la polarisation) : WHITE moyen {pp(d, "WHITEJ", 0.05)[1]:.2f} V, PINK moyen {pp(d, "PINKJ", 0.05)[1]:.2f} V (doivent être ≈ 0 V)')

def SHLAG():
    d = sim('SHLAG', 'clk', T('SHLAG', 0.4, step=20e-6, osc=True, drive={'J2': 'SIN(0 5 3)'}, pots={'RV1': 0.6, 'RV2': 0.3, 'RV3': 0.3}), ['CLOCKJ', 'SHOUTJ', 'GATEJ', 'LAGOUTJ', 'NOISEJ'])
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
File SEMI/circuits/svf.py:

"""ocTavio SEMI - STATE VARIABLE 12 dB (Oberheim SEM style mode : LP -> NOTCH -> HP, BP switch).
SPICE netlist of the circuit, with the sliders as parameters. Used by test_circuits.py.

Signal (all levels Eurorack) :
  U1A  inverting summer : HP = -(IN + LP + d*BP)          R1 20k (IN), R2 20k (LP), R3 10k (damping), R4 20k feedback,
                          D1/D2 BZT52C5V1 back to back + R25 4.7k from BP : extra damping above ~5.7 V = the self-oscillation stays near +/-6 V
  OTA1 (LM13700 A) + C1 470p + U1B follower : BP = integral of HP     input divider R5 22k / R6 220, R7 220 on the - input
  OTA2 (LM13700 B) + C2 470p + U1C follower : LP = integral of BP     R8 22k / R9 220, R10 220
  RESONANCE slider RV2 10k B : BP on the bottom end, GND on the top, wiper -> R3 : damping 2 (Q 0.5) -> 0
  R23 20k / R24 100 : a little BP on the + input of U1A = slightly negative damping at the top of RESONANCE -> sure self-oscillation
  MODE slider RV3 10k B between LP (bottom) and HP (top), wiper = LP / NOTCH / HP ; SW1 BP switch picks BP instead
  U1D inverting x1 (R11 20k, R12 20k) -> R13 1k -> OUT
Frequency :
  U2A summer : FREQ slider RV1 10k B (0..12 V) via R14 158k, ENV (jack -> ENV slider RV4 100k A) via R15 165k,
               MOD (jack -> MOD slider RV5 100k B) via R16 267k, offset R17 357k from -12 V, R18 100k feedback
  R19 4.12k / R20 100 divider -> base of Q1b (BCM857DS) ; Q1a reference : base GND, collector held at 0 V by U2B,
  R21 1.2M to -12 V -> Iref 10 uA ; U2B drives the common emitters through R22 1k, C3 100p
  Q1b collector -> IABC of both OTAs tied together (same die : the current splits evenly)
  -> about 20 Hz (FREQ 0) to 20 kHz (FREQ 10), ENV 0.8 oct/V and MOD 0.5 oct/V at full slider.
"""
import os, sys
H = os.path.dirname(os.path.abspath(__file__)); sys.path.insert(0, os.path.join(H, '..', '..', 'outils', 'spice'))
from kicad2spice import MODELS

def pot(name, a, w, b, R, x, log=False):
    x = min(max(x, 0.001), 0.999)
    if log: x = min(max((100 ** x - 1) / 99, 0.0005), 0.999)
    return f"R{name}a {a} {w} {R * x:.6g}\nR{name}b {w} {b} {R * (1 - x):.6g}\n"

def netlist(freq=0.5, reso=0.0, mode=0.0, bp=False, env_amt=0.0, mod_amt=0.0, vin='DC 0', venv='DC 0', vmod='DC 0', analysis='', probes=''):
    n = MODELS + "\n* ---- SVF\nVP P12 0 DC 12\nVM M12 0 DC -12\n"
    n += f"VIN IN 0 {vin}\nVENV ENVJ 0 {venv}\nVMOD MODJ 0 {vmod}\n"
    # summer / damping
    n += "R1 IN SUMN 20k\nR2 LP SUMN 20k\nR3 DW SUMN 10k\nR4 SUMN HP 20k\nD1 ZK BP DZ5V1\nD2 ZK ZL DZ5V1\nR25 ZL SUMN 4.7k\n"
    n += "R23 BP SUMP 20k\nR24 SUMP 0 100\nXU1A SUMP SUMN HP P12 M12 TL07X\n"
    n += pot('RV2', 'BP', 'DW', '0', 10e3, reso)
    # integrators (LM13700 pins : inp inn iabc db bin bout out vp vn)
    n += "R5 HP O1P 22k\nR6 O1P 0 220\nR7 O1N 0 220\nXOTA1 O1P O1N IABC NC1 NC2 NC3 C1N P12 M12 LM13700H\nC1 C1N 0 470p\nXU1B C1N BP BP P12 M12 TL07X\n"
    n += "R8 BP O2P 22k\nR9 O2P 0 220\nR10 O2N 0 220\nXOTA2 O2P O2N IABC NC4 NC5 NC6 C2N P12 M12 LM13700H\nC2 C2N 0 470p\nXU1C C2N LP LP P12 M12 TL07X\n"
    # mode
    n += pot('RV3', 'LP', 'MW', 'HP', 10e3, mode)
    n += f"RSW1 {'BP' if bp else 'MW'} SEL 0.01\nR11 SEL ON 20k\nR12 ON OB 20k\nXU1D 0 ON OB P12 M12 TL07X\nR13 OB OUT 1k\nRL OUT 0 100k\n"
    # frequency CV
    n += pot('RV1', '0', 'FW', 'P12', 10e3, freq)
    n += pot('RV4', '0', 'EW', 'ENVJ', 100e3, env_amt, log=True) + pot('RV5', '0', 'MW5', 'MODJ', 100e3, mod_amt)
    n += "R14 FW CVN 158k\nR15 EW CVN 165k\nR16 MW5 CVN 267k\nR17 M12 CVN 357k\nR18 CVN CVO 100k\nXU2A 0 CVN CVO P12 M12 TL07X\n"
    n += "R19 CVO QB 4.12k\nR20 QB 0 100\n"
    n += "Q1a QRC 0 QE BC857\nQ1b IABC QB QE BC857\nR21 QRC M12 1.2Meg\nC3 QE_D QRC 100p\nXU2B 0 QRC QE_D P12 M12 TL07X\nR22 QE_D QE 1k\n"
    n += analysis + "\n" + probes + "\n.options method=gear reltol=1e-4 abstol=1e-12 vntol=1e-6 itl4=200\n.end\n"
    return n
